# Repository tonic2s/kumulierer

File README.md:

# Kumulierer
## Description
Li-Ion battery charger with basic protection, usb-c input / 2-pin output &amp; power path

## Links
[Aisler Project](https://aisler.net/p/CNVPTRAD)

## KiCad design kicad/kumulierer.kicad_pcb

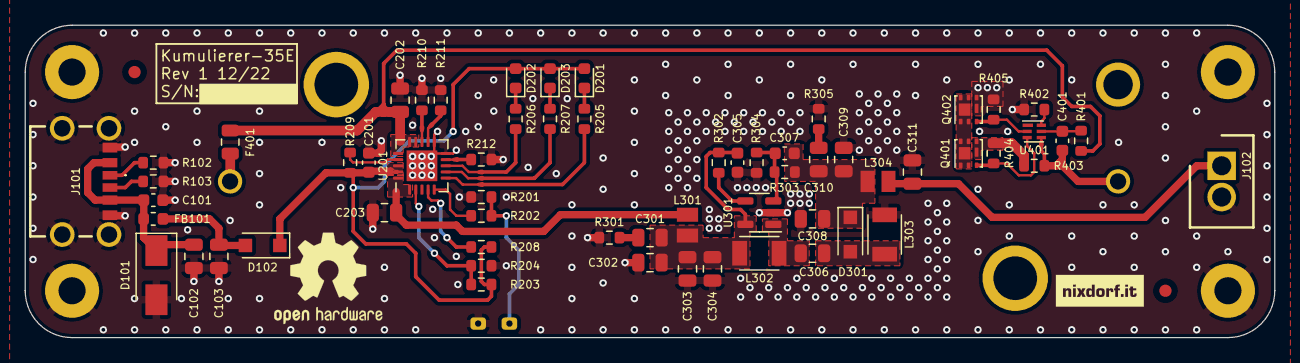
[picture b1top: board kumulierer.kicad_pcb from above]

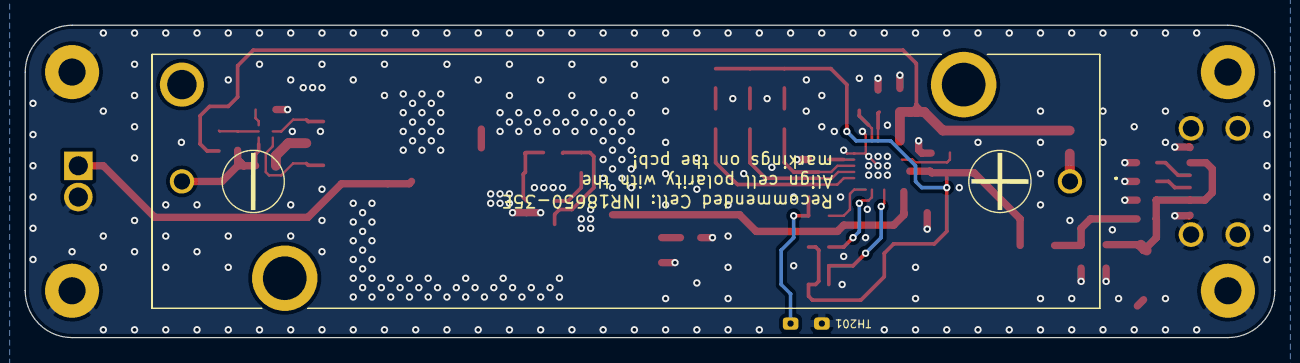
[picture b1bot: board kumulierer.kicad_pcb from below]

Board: 2 copper layers, 101.6 x 25.4 mm, 69 parts (2 on the bottom side), 39 nets.

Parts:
BT401: 18650-35E; 1043_Battery_holder_18650
C101, C201, C305, C401: 100n; C_0603_1608Metric
C102, C103, C202, C203, C301, C302, C303, C304, C306, C308, C309, C310, C311: 10u; C_0805_2012Metric
C307: 2n2; C_0603_1608Metric
D101: SMA 5V; D_SMA
D102, D301: ACDBMS240-HF; D_SOD-123F
D201, D202, D203: RED; LED_0603_1608Metric
F401: 6A; Fuse_0805_2012Metric
FB101: 220; L_0603_1608Metric
FID101, FID102: Fiducial; Fiducial_1mm_Mask2mm
H101, H102, H103, H104: M2; MountingHole_2.2mm_M2_Pad
J101: USB4125-GF-A; USB4125GFA
J102: 6-440054-2; 6-440054-2 2 Pin Header
L301, L304: 470nH; IND_0806_2016
L302, L303: 3.3uH; L_TDK_NLV32_3.2x2.5mm
Q401, Q402: CSD17313Q2; Texas_DQK
R102, R103: 5k1; R_0603_1608Metric
R201, R202, R403: 0; R_0603_1608Metric
R203: 330k; R_0603_1608Metric
R204: 110k; R_0603_1608Metric
R205, R206, R207, R208, R209, R212: 1k; R_0603_1608Metric
R210, R402: 2k2; R_0603_1608Metric
R211: 22k; R_0603_1608Metric
R301, R305: .47; R_0603_1608Metric
R302: 100k; R_0603_1608Metric
R303: 16k2; R_0603_1608Metric
R304: 10k; R_0603_1608Metric
R401: 330; R_0603_1608Metric
R404, R405: 5M; R_0603_1608Metric
TH201: 10k; NRL1104J3380B1F
U201: MCP73871-2CC; QFN-20-1EP_4x4mm_P0.5mm_EP2.5x2.5mm
U301: LMR62421XMF; SOT-23-5
U401: BQ297xy; WSON-6_1.5x1.5mm_P0.5mm

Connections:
+3V3: C311.1, J102.1, L304.2
+3V8: C202.1, F401.2, R401.2, U201.14 (VBAT), U201.15 (VBAT), U201.16 (Vbat_SENSE)
/BAT+: BT401.1 (+), F401.1
/BAT-: BT401.2 (-), C401.2, R403.1, U401.4 (VSS)
/CC1: J101.A5 (CC1), R102.1
/CC2: J101.B5 (CC2), R103.1
/CE: R209.2, U201.17 (CE)
/PG: R205.2, U201.6 (~PG)
/PROG1: R210.2, U201.13 (PROG1)
/PROG2: R208.2, U201.4 (PROG2)
/PROG3: R211.2, U201.12 (PROG3)
/STAT1: R206.2, U201.8 (STAT1/~LBO)
/STAT2: R207.2, U201.7 (STAT2)
/TE: R212.1, U201.9 (~TE)
GND: C101.2, C102.2, C103.2, C201.2, C202.2, C203.2, C302.2, C303.2, C304.2, C305.1, C308.2, C309.2, C311.2, D101.2 (A), H101.1, H102.1, H103.1, H104.1, J101.A12 (GND), J101.B12 (GND), J101.S1 (SHIELD), J102.2, L303.2, Q402.4 (S), Q402.7 (S), R102.2, R103.2, R201.2, R204.1, R210.1, R211.1, R212.2, R301.2, R304.1, R305.2, R402.1, R405.2, TH201.2, U201.10 (VSS), U201.11 (VSS), U201.21 (VSS), U301.2 (GND)
unnamed: C101.1, C102.1, D101.1 (K), FB101.1, J101.A9 (VBUS), J101.B9 (VBUS)
unnamed: C103.1, D102.2 (A), FB101.2
unnamed: C301.1, C302.1, C303.1, C304.1, C305.2, L301.2, L302.1, R302.1, U301.5 (VIN)
unnamed: C301.2, R301.1
unnamed: C306.1, L302.2, U301.1 (SW)
unnamed: C306.2, D301.2 (A), L303.1
unnamed: C307.1, C308.1, C309.1, C310.1, D301.1 (K), L304.1, R303.2
unnamed: C307.2, R303.1, R304.2, U301.3 (FB)
unnamed: C310.2, R305.1
unnamed: C401.1, R401.1, U401.5 (BAT)
unnamed: D201.1 (K), R205.1
unnamed: D202.1 (K), R206.1
unnamed: D203.1 (K), R207.1
unnamed: Q401.1 (D), Q401.2 (D), Q401.5 (D), Q401.6 (D), Q401.8 (D), Q402.1 (D), Q402.2 (D), Q402.5 (D), Q402.6 (D), Q402.8 (D)
unnamed: Q401.3 (G), R404.1, U401.3 (Dout)
unnamed: Q401.4 (S), Q401.7 (S), R403.2, R404.2
unnamed: Q402.3 (G), R405.1, U401.2 (Cout)
unnamed: R201.1, R202.2, TH201.1
unnamed: R202.1, U201.5 (THERM)
unnamed: R203.1, R204.2, U201.2 (VPCC)
unnamed: R302.2, U301.4 (EN)
unnamed: R402.2, U401.6 (V-)
VBUS: C201.1, D102.1 (K), D201.2 (A), D202.2 (A), D203.2 (A), R203.2, R208.1, R209.1, U201.18 (IN), U201.19 (IN)
VCC: C203.1, L301.1, U201.1 (OUT), U201.20 (OUT)

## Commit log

2023-01-04 Added .gitIgnore & updated files
2023-01-07 Add interactive bom; fix schematic & pcb
